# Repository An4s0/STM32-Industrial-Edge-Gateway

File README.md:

# STM32 Industrial Edge Gateway

**An Ethernet-Based Environmental Monitoring System for Kunak AIR
Sensors**

An embedded industrial edge gateway built on the **STM32F767ZI** that
acquires environmental measurements from a **Kunak AIR** sensor using
**Modbus RTU over RS485**, processes the collected data, calculates the
**US Air Quality Index (AQI)**, stores historical records on an SD card,
and serves a real-time web dashboard over Ethernet.

The system operates entirely on a local network without requiring cloud
services, external APIs, or internet connectivity, making it suitable
for industrial monitoring and edge computing applications.

------------------------------------------------------------------------

# Features

-   Real-time environmental monitoring
-   Modbus RTU Master implementation over RS485
-   Ethernet-based embedded web server (LwIP HTTPD)
-   Dynamic web pages using SSI (Server Side Includes)
-   Local data logging to SD card (FATFS)
-   CSV export for historical measurements
-   US Air Quality Index (AQI) calculation
-   Live browser-based dashboard
-   Bilingual user interface (English / Arabic)
-   Automatic language switching
-   Sensor communication monitoring
-   Industrial status indication using LEDs
-   Fully offline operation (No Cloud Required)

------------------------------------------------------------------------

# System Architecture

``` text
                  +----------------------+
                  |      Kunak AIR       |
                  | Environmental Sensor |
                  +----------+-----------+
                             |
                     Modbus RTU (RS485)
                             |
                STM32 Industrial Edge Gateway
                             |
        +--------------------+--------------------+
        |                                         |
   SD Card Logging                       Embedded Web Server
        |                                         |
      FATFS                                  LwIP HTTPD
        |                                         |
        +--------------------+--------------------+
                             |
                      Ethernet Network
                             |
                     Web Browser Dashboard
```

------------------------------------------------------------------------

# System Workflow

1.  Poll the Kunak AIR sensor every **10 seconds** using Modbus RTU.
2.  Read environmental measurements.
3.  Convert raw register values into engineering units.
4.  Calculate the US AQI from PM2.5 and PM10.
5.  Store measurements on the SD card as CSV records.
6.  Update the embedded web dashboard.
7.  Serve the dashboard over the local Ethernet network.

------------------------------------------------------------------------

# Measured Parameters

-   Temperature
-   Humidity
-   Pressure
-   PM1
-   PM2.5
-   PM10
-   US AQI

------------------------------------------------------------------------

# Dashboard Features

-   Real-time environmental data
-   AQI visualization
-   Automatic data refresh
-   Local Ethernet access
-   Responsive design
-   English and Arabic interface
-   AQI status indication using EPA color categories

------------------------------------------------------------------------

# Data Logging

Example CSV record:

``` text
Timestamp,Temperature,Humidity,Pressure,PM1,PM2.5,PM10,AQI
2026-06-14 12:00:00,31.20,46.00,1012.0,12.5,18.3,25.7,72
```

------------------------------------------------------------------------

# Reliability Features

-   Modbus CRC16 verification
-   Communication timeout detection
-   Sensor offline monitoring
-   Runtime status indication using LEDs
-   Watchdog-based recovery support
-   Local data storage without internet dependency

------------------------------------------------------------------------

# Technologies Used

-   Embedded Systems
-   Industrial IoT (IIoT)
-   Edge Computing
-   STM32
-   Modbus RTU
-   RS485
-   Ethernet
-   LwIP
-   FATFS
-   Embedded Web Server
-   Data Logging

------------------------------------------------------------------------

<br/>

**Keep building. Keep learning.**

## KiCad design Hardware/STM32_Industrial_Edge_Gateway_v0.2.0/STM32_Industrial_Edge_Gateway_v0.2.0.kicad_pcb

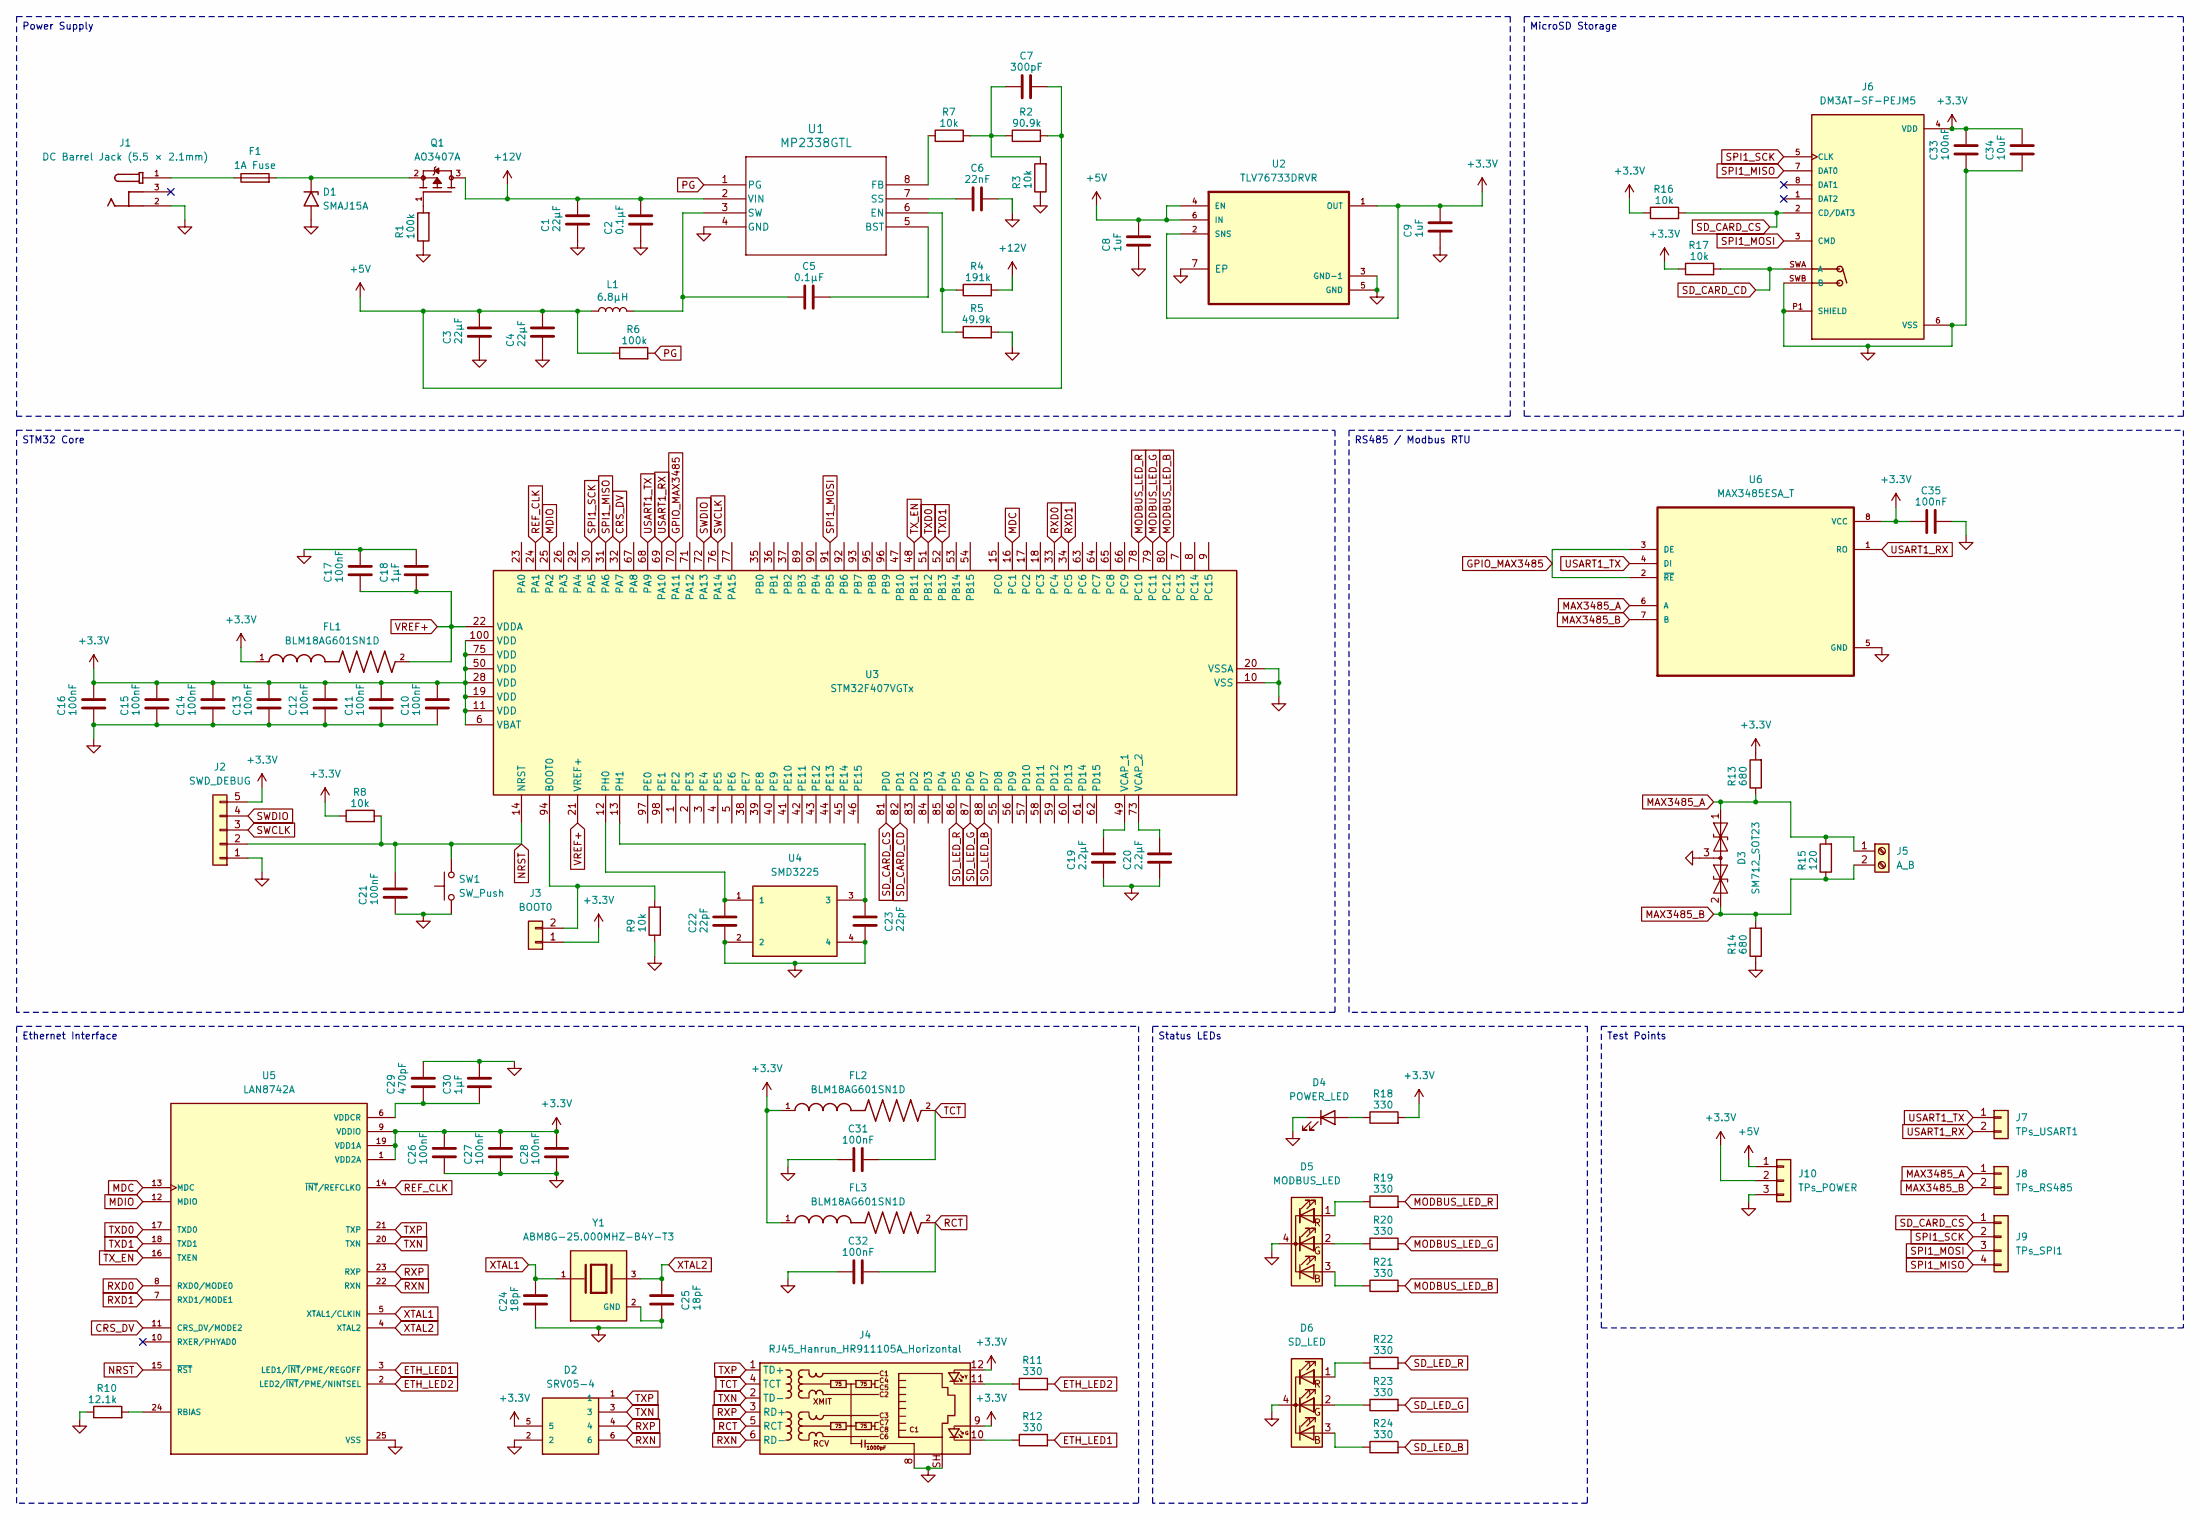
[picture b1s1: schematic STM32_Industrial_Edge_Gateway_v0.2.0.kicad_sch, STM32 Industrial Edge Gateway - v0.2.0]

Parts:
C1, C3, C4: 22μF; C_0603_1608Metric
C2, C5: 0.1μF; C_0603_1608Metric
C6: 22nF; C_0603_1608Metric
C7: 300pF; C_0603_1608Metric
C8, C9: 1uF; C_0603_1608Metric
C10, C11, C12, C13, C14, C15, C16, C17, C21, C26, C27, C28, C31, C32, C33, C35: 100nF; C_0603_1608Metric
C18, C30: 1µF; C_0603_1608Metric
C19, C20: 2.2µF; C_0603_1608Metric
C22, C23: 22pF; C_0603_1608Metric
C24, C25: 18pF; C_0603_1608Metric
C29: 470pF; C_0603_1608Metric
C34: 10uF; C_0603_1608Metric
D1: SMAJ15A; D_SMA
D2: SRV05-4; SOT95P280X145-6N; MOUSER_PART_NUMBER 947-SRV05-4.TCT
D3: SM712_SOT23; SOT-23
D4: POWER_LED; LED_0603_1608Metric
D5: MODBUS_LED; LED_RGB_1210
D6: SD_LED; LED_RGB_1210
F1: 1A Fuse; Fuse_1206_3216Metric
FL1, FL2, FL3: BLM18AG601SN1D; BEADC1608X95N
J1: DC Barrel Jack (5.5 × 2.1mm); EJ503A; PARTREV B
J2: SWD_DEBUG; PinHeader_1x05_P2.54mm_Vertical
J3: BOOT0; PinHeader_1x02_P2.54mm_Vertical
J4: RJ45_Hanrun_HR911105A_Horizontal
J5: A_B; TerminalBlock_Phoenix_MKDS-1,5-2-5.08_1x02_P5.08mm_Horizont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
J6: DM3AT-SF-PEJM5; HRS_DM3AT-SF-PEJM5; PARTREV 20200913
J7: TPs_USART1; PinHeader_1x02_P2.54mm_Vertical
J8: TPs_RS485; PinHeader_1x02_P2.54mm_Vertical
J9: TPs_SPI1; PinHeader_1x04_P2.54mm_Vertical
J10: TPs_POWER; PinHeader_1x03_P2.54mm_Vertical
L1: 6.8μH; L_0805_2012Metric
Q1: AO3407A; PARTREV 5
R1, R6: 100k; R_0603_1608Metric
R2: 90.9k; R_0603_1608Metric
R3, R7, R8, R9, R16, R17: 10k; R_0603_1608Metric
R4: 191k; R_0603_1608Metric
R5: 49.9k; R_0603_1608Metric
R10: 12.1k; R_0603_1608Metric
R11, R12, R18, R19, R20, R21, R22, R23, R24: 330; R_0603_1608Metric
R13, R14: 680; R_0603_1608Metric
R15: 120; R_0603_1608Metric
SW1: SW_Push; SW_SPST_TL3342
U1: MP2338GTL
U2: TLV76733DRVR; SON65P200X200X80-7N
U3: STM32F407VGTx; LQFP-100_14x14mm_P0.5mm
U4: SMD3225
U5: LAN8742A; LAN8742A-CZ-TR; PARTREV A
U6: MAX3485ESA_T; SOIC127P600X175-8N
Y1: ABM8G-25.000MHZ-B4Y-T3; XTAL_ABM8G-25.000MHZ-B4Y-T3; PARTREV 08.13.15

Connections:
+3.3V: C9.1, C10.1, C11.1, C12.1, C13.1, C14.1, C15.1, C16.1, C26.1, C27.1, C28.1, C33.1, C34.1, C35.1, D2.5, FL1.1, FL2.1, FL3.1, J2.5, J3.1, J4.9, J4.12, J6.4 (VDD), J10.2, R8.1, R13.2, R16.1, R17.1, R18.2, U2.1 (OUT), U2.2 (SNS), U3.6 (VBAT), U3.11 (VDD), U3.19 (VDD), U3.28 (VDD), U3.50 (VDD), U3.75 (VDD), U3.100 (VDD), U5.1 (VDD2A), U5.9 (VDDIO), U5.19 (VDD1A), U6.8 (VCC)
+5V: C3.1, C4.1, C7.2, C8.1, J10.1, L1.1, R2.2, R6.1, U2.4 (EN), U2.6 (IN)
+12V: C1.1, C2.1, Q1.3, R4.2, U1.2 (VIN)
CRS_DV: U3.32 (PA7), U5.11 (CRS_DV/MODE2)
ETH_LED1: R12.2, U5.3 (LED1/~INT/PME/REGOFF)
ETH_LED2: R11.2, U5.2 (LED2/~INT/PME/NINTSEL)
GND: C1.2, C2.2, C3.2, C4.2, C6.2, C8.2, C9.2, C10.2, C11.2, C12.2, C13.2, C14.2, C15.2, C16.2, C17.1, C18.1, C19.2, C20.2, C21.2, C22.2, C23.1, C24.2, C25.1, C26.2, C27.2, C28.2, C29.1, C30.1, C31.1, C32.1, C33.2, C34.2, C35.2, D1.2 (A2), D2.2, D3.3 (common), D4.1 (K), D5.4 (K), D6.4 (K), J1.2, J2.1, J4.8, J4.SH, J6.6 (VSS), J6.P1 (SHIELD), J6.P2 (SHIELD), J6.P3 (SHIELD), J6.P4 (SHIELD), J6.SWB (B), J10.3, R1.1, R3.1, R5.2, R9.1, R10.1, R14.1, SW1.1, U1.4 (GND), U2.3 (GND-1), U2.5 (GND), U2.7 (EP), U3.10 (VSS), U3.20 (VSSA), U3.27 (VSS), U3.74 (VSS), U3.99 (VSS), U4.2, U4.4, U5.25 (VSS), U6.5 (GND), Y1.2 (GND), Y1.4 (GND)
GPIO_MAX3485: U3.70 (PA11), U6.2 (~RE), U6.3 (DE)
MAX3485_A: D3.1 (A1), J5.1, J8.1, R13.1, R15.2, U6.6 (A)
MAX3485_B: D3.2 (A2), J5.2, J8.2, R14.2, R15.1, U6.7 (B)
MDC: U3.16 (PC1), U5.13 (MDC)
MDIO: U3.25 (PA2), U5.12 (MDIO)
MODBUS_LED_B: R21.2, U3.80 (PC12)
MODBUS_LED_G: R20.2, U3.79 (PC11)
MODBUS_LED_R: R19.2, U3.78 (PC10)
NRST: C21.1, J2.2, R8.2, SW1.2, U3.14 (NRST), U5.15 (~RST)
unnamed: C7.1, R2.1, R3.2, R7.2
unnamed: D1.1 (A1), F1.2, Q1.2
unnamed: D4.2 (A), R18.1
unnamed: D5.3 (BA), R21.1
unnamed: D5.2 (GA), R20.1
unnamed: D5.1 (RA), R19.1
unnamed: D6.3 (BA), R24.1
unnamed: D6.2 (GA), R23.1
unnamed: D6.1 (RA), R22.1
unnamed: F1.1, J1.1
unnamed: J3.2, R9.2, U3.94 (BOOT0)
unnamed: J4.10, R12.1
unnamed: J4.11, R11.1
unnamed: Q1.1, R1.2
unnamed: C5.2, U1.5 (BST)
unnamed: R4.1, R5.1, U1.6 (EN)
unnamed: R7.1, U1.8 (FB)
unnamed: C6.1, U1.7 (SS)
unnamed: C5.1, L1.2, U1.3 (SW)
unnamed: C22.1, U3.12 (PH0), U4.1
unnamed: C23.2, U3.13 (PH1), U4.3
unnamed: C19.1, U3.49 (VCAP_1)
unnamed: C20.1, U3.73 (VCAP_2)
unnamed: R10.2, U5.24 (RBIAS)
unnamed: C29.2, C30.2, U5.6 (VDDCR)
PG: R6.2, U1.1 (PG)
RCT: C32.2, FL3.2, J4.5 (RCT)
REF_CLK: U3.24 (PA1), U5.14 (~INT/REFCLKO)
RXD0: U3.33 (PC4), U5.8 (RXD0/MODE0)
RXD1: U3.34 (PC5), U5.7 (RXD1/MODE1)
RXN: D2.6, J4.6 (RD-), U5.22 (RXN)
RXP: D2.4, J4.3 (RD+), U5.23 (RXP)
SD_CARD_CD: J6.SWA (A), R17.2, U3.82 (PD1)
SD_CARD_CS: J6.2 (CD/DAT3), J9.1, R16.2, U3.81 (PD0)
SD_LED_B: R24.2, U3.88 (PD7)
SD_LED_G: R23.2, U3.87 (PD6)
SD_LED_R: R22.2, U3.86 (PD5)
SPI1_MISO: J6.7 (DAT0), J9.4, U3.31 (PA6)
SPI1_MOSI: J6.3 (CMD), J9.3, U3.91 (PB5)
SPI1_SCK: J6.5 (CLK), J9.2, U3.30 (PA5)
SWCLK: J2.3, U3.76 (PA14)
SWDIO: J2.4, U3.72 (PA13)
TCT: C31.2, FL2.2, J4.4 (TCT)
TXD0: U3.51 (PB12), U5.17 (TXD0)
TXD1: U3.52 (PB13), U5.18 (TXD1)
TXN: D2.3, J4.2 (TD-), U5.20 (TXN)
TXP: D2.1, J4.1 (TD+), U5.21 (TXP)
TX_EN: U3.48 (PB11), U5.16 (TXEN)
USART1_RX: J7.2, U3.69 (PA10), U6.1 (RO)
USART1_TX: J7.1, U3.68 (PA9), U6.4 (DI)
VREF+: C17.2, C18.2, FL1.2, U3.21 (VREF+), U3.22 (VDDA)
XTAL1: C24.1, U5.5 (XTAL1/CLKIN), Y1.1
XTAL2: C25.2, U5.4 (XTAL2), Y1.3

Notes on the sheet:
Ethernet Interface
MicroSD Storage
Power Supply
STM32 Core
RS485 / Modbus RTU
Status LEDs
Test Points

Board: 2 copper layers, 89 parts (0 on the bottom side), 69 nets, no tracks yet.

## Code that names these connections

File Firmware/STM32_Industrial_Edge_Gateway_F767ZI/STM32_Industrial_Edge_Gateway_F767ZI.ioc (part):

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Mcu.Name=STM32F767ZITx
Mcu.Package=LQFP144
Mcu.UserName=STM32F767ZITx
PA1.Mode=RMII
PA1.Signal=ETH_REF_CLK
PA13.Mode=Serial_Wire
PA13.Signal=SYS_JTMS-SWDIO
PA14.Mode=Serial_Wire
PA14.Signal=SYS_JTCK-SWCLK
PA2.Mode=RMII
PA2.Signal=ETH_MDIO
PA3.Signal=GPIO_Output
PA5.Mode=Full_Duplex_Master
PA5.Signal=SPI1_SCK
PA6.Mode=Full_Duplex_Master
PA6.Signal=SPI1_MISO
PA7.Mode=RMII
PA7.Signal=ETH_CRS_DV
PB13.Mode=RMII
PB13.Signal=ETH_TXD1
PC0.Signal=GPIO_Output
PC1.Mode=RMII
PC1.Signal=ETH_MDC
PC4.Mode=RMII
PC4.Signal=ETH_RXD0
PC5.Mode=RMII
PC5.Signal=ETH_RXD1
PD0.Mode=Asynchronous
PD0.Signal=UART4_RX
PD1.Mode=Asynchronous
PD1.Signal=UART4_TX
PD7.Mode=Full_Duplex_Master
PD7.Signal=SPI1_MOSI
PD8.Mode=Asynchronous
PD8.Signal=USART3_TX
PD9.Mode=Asynchronous
PD9.Signal=USART3_RX
PF10.GPIOParameters=GPIO_Speed,PinState
PF10.GPIO_Speed=GPIO_SPEED_FREQ_HIGH
PF10.PinState=GPIO_PIN_SET
PF10.Signal=GPIO_Output
PF5.Signal=GPIO_Output
PG11.Mode=RMII
PG11.Signal=ETH_TX_EN
PG13.Mode=RMII
PG13.Signal=ETH_TXD0
PH0/OSC_IN.Mode=HSE-External-Oscillator
PH0/OSC_IN.Signal=RCC_OSC_IN
PH1/OSC_OUT.Mode=HSE-External-Oscillator
PH1/OSC_OUT.Signal=RCC_OSC_OUT
RCC.HSE_VALUE=8000000
RCC.SYSCLKFreq_VALUE=128000000
RCC.SYSCLKSource=RCC_SYSCLKSOURCE_PLLCLK
RCC.SYSCLKSourceVirtual=RCC_SYSCLKSOURCE_PLLCLK
board=NUCLEO-F767ZI
boardIOC=true
